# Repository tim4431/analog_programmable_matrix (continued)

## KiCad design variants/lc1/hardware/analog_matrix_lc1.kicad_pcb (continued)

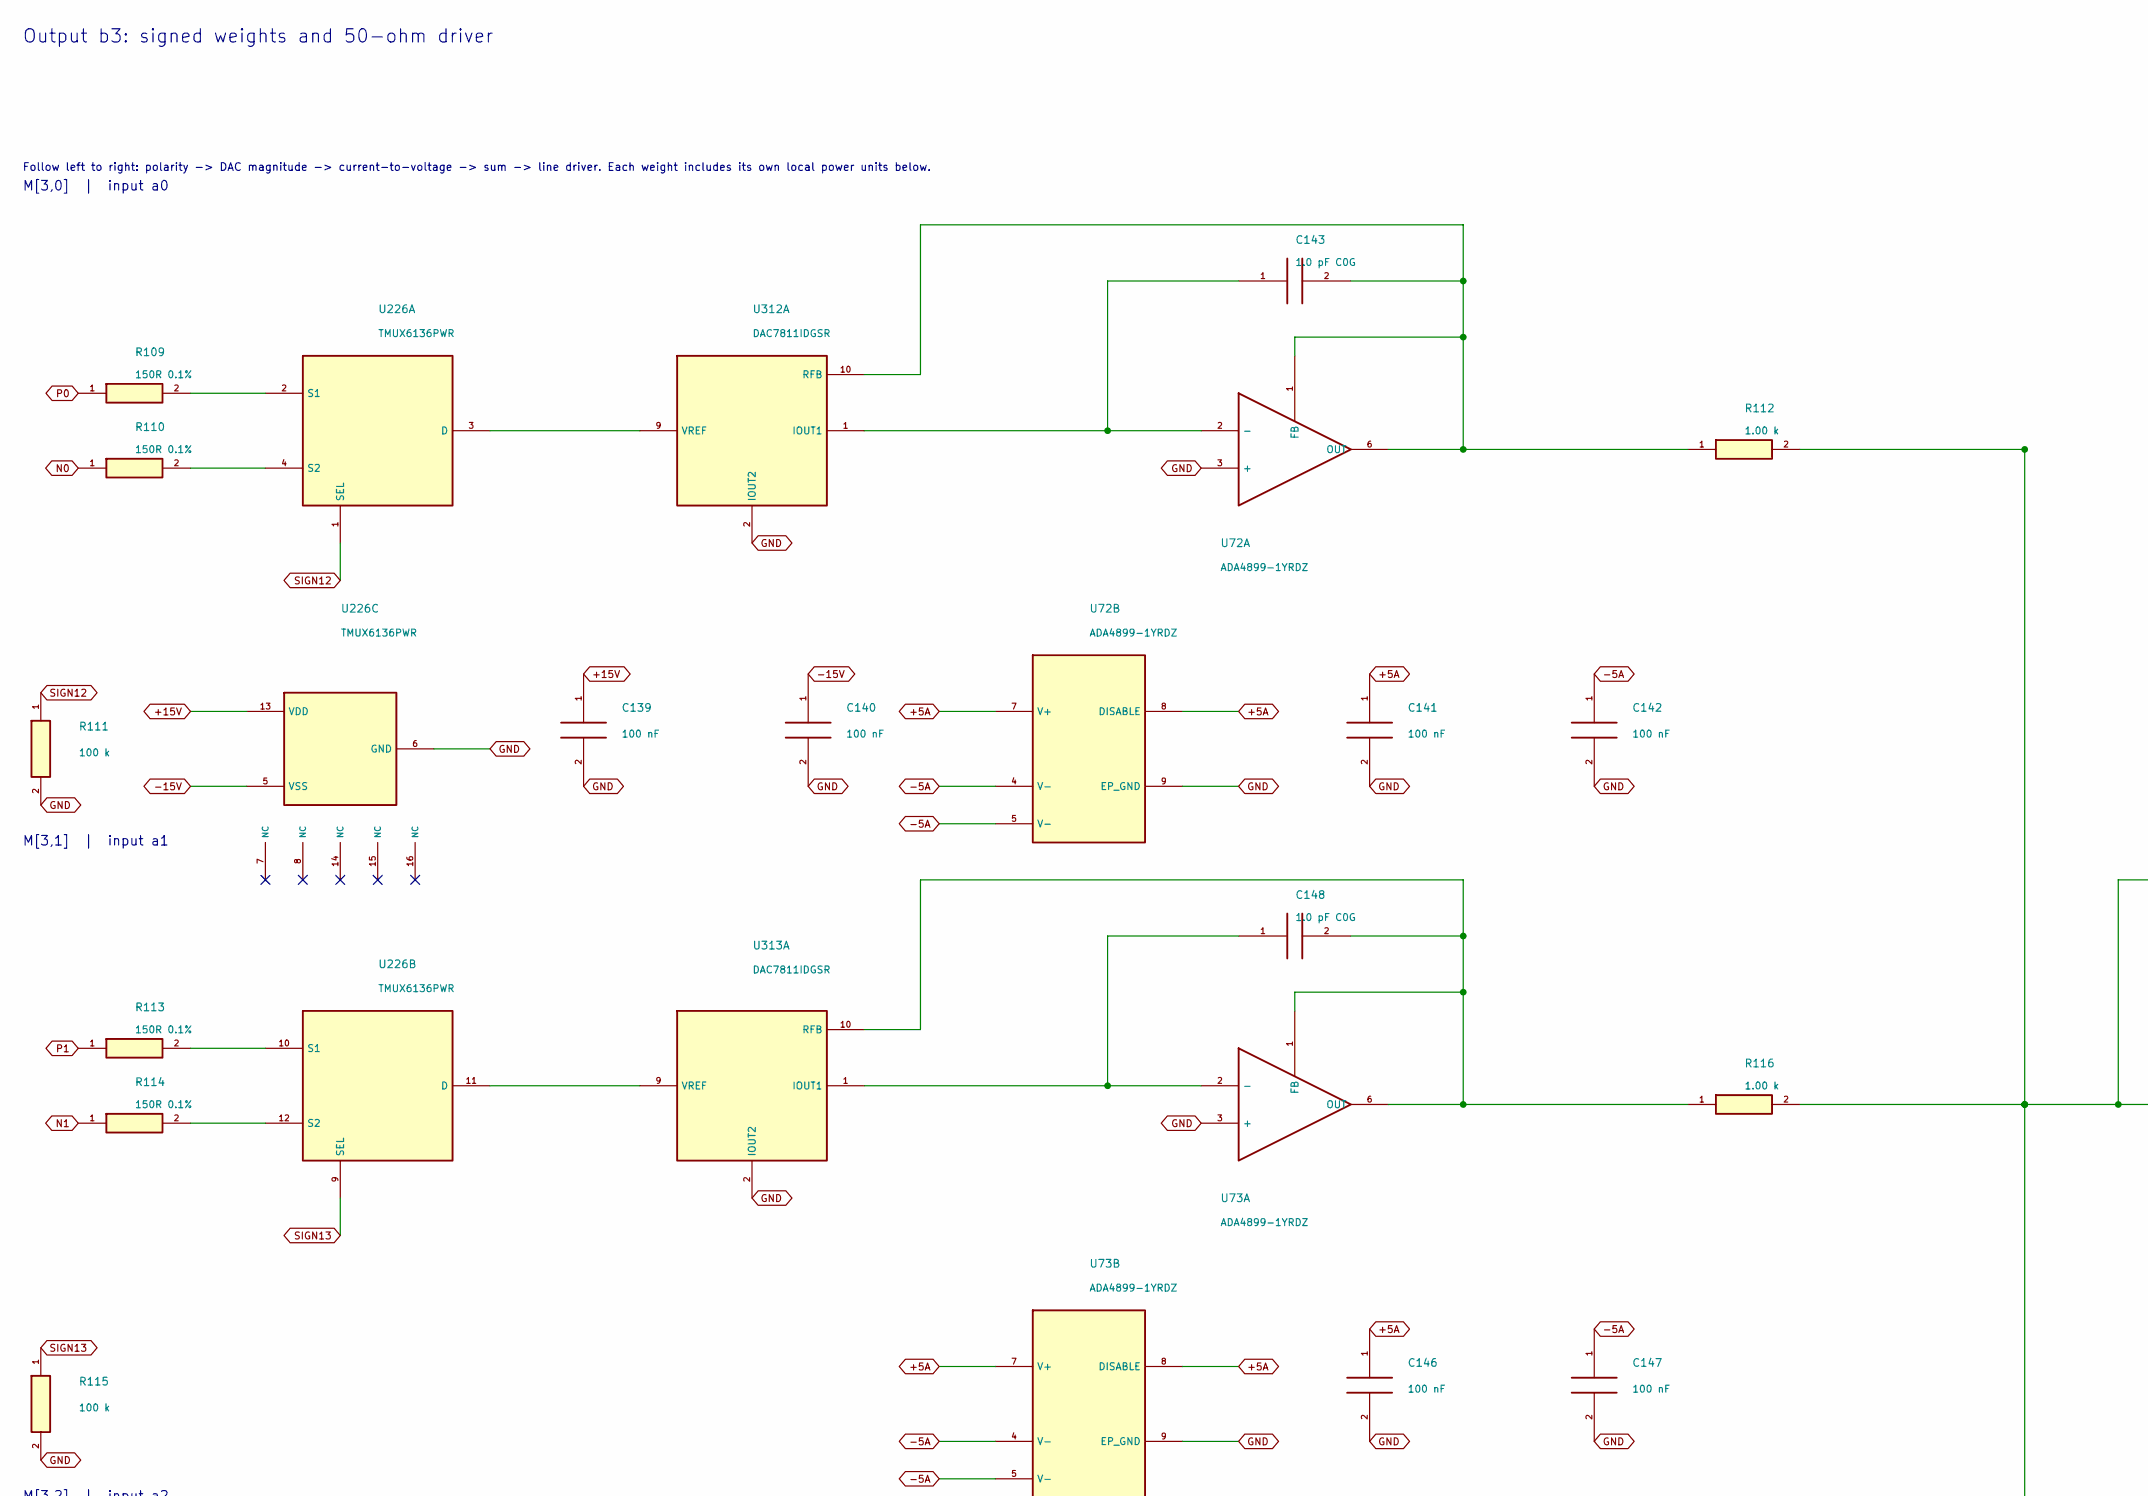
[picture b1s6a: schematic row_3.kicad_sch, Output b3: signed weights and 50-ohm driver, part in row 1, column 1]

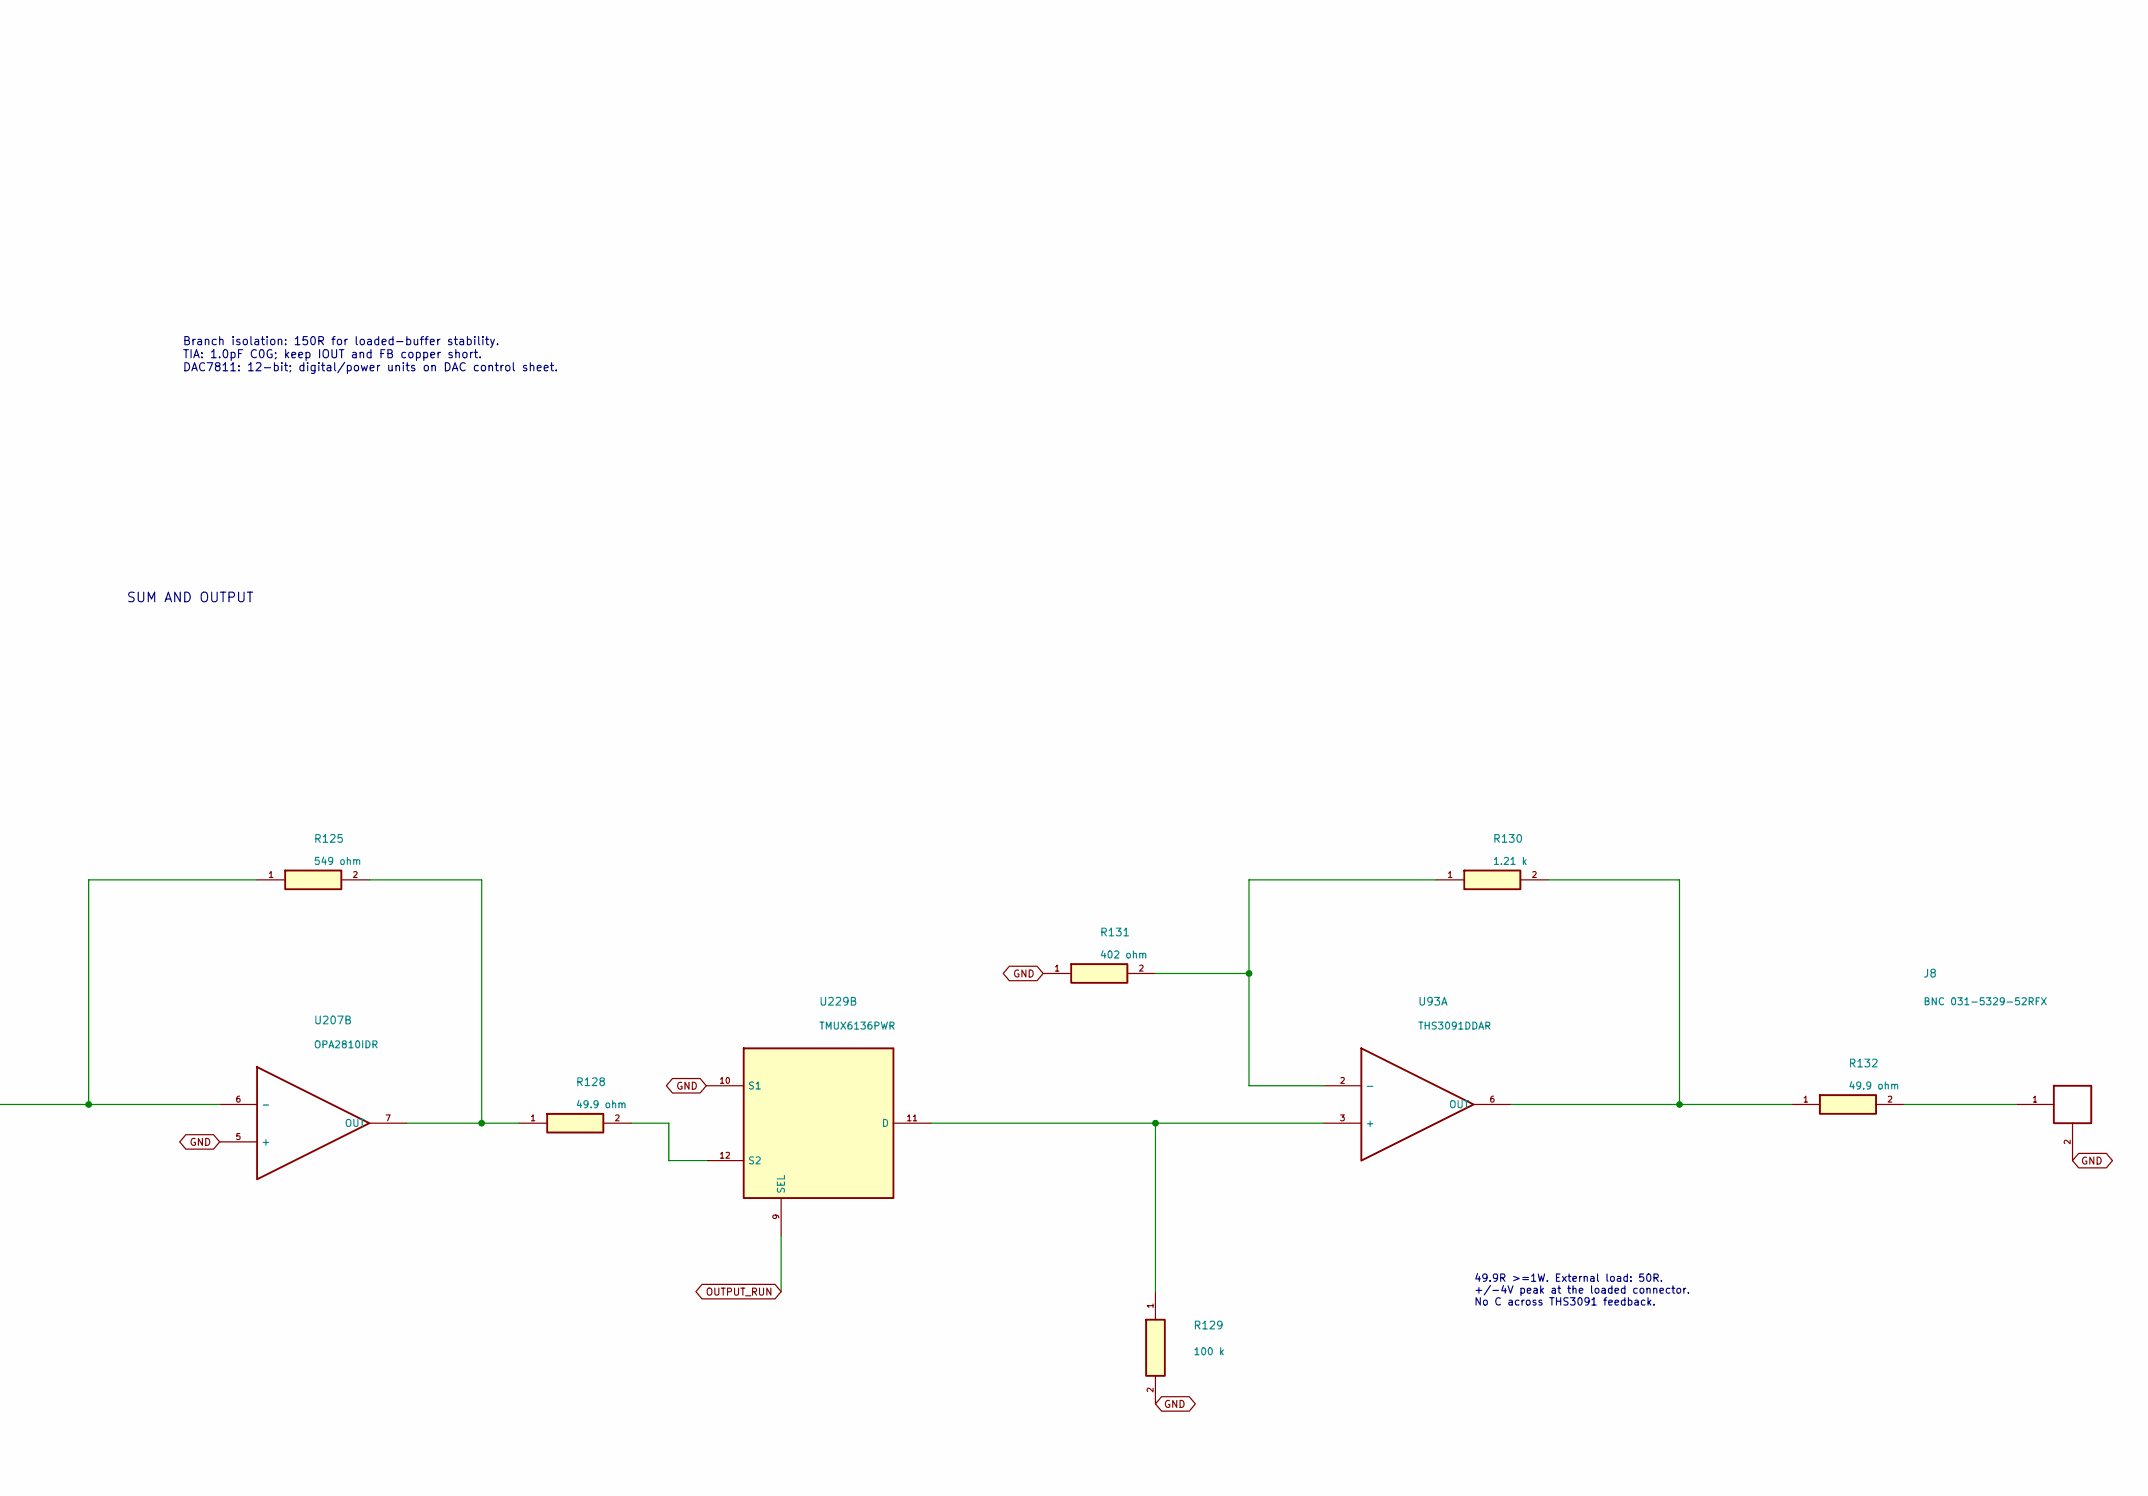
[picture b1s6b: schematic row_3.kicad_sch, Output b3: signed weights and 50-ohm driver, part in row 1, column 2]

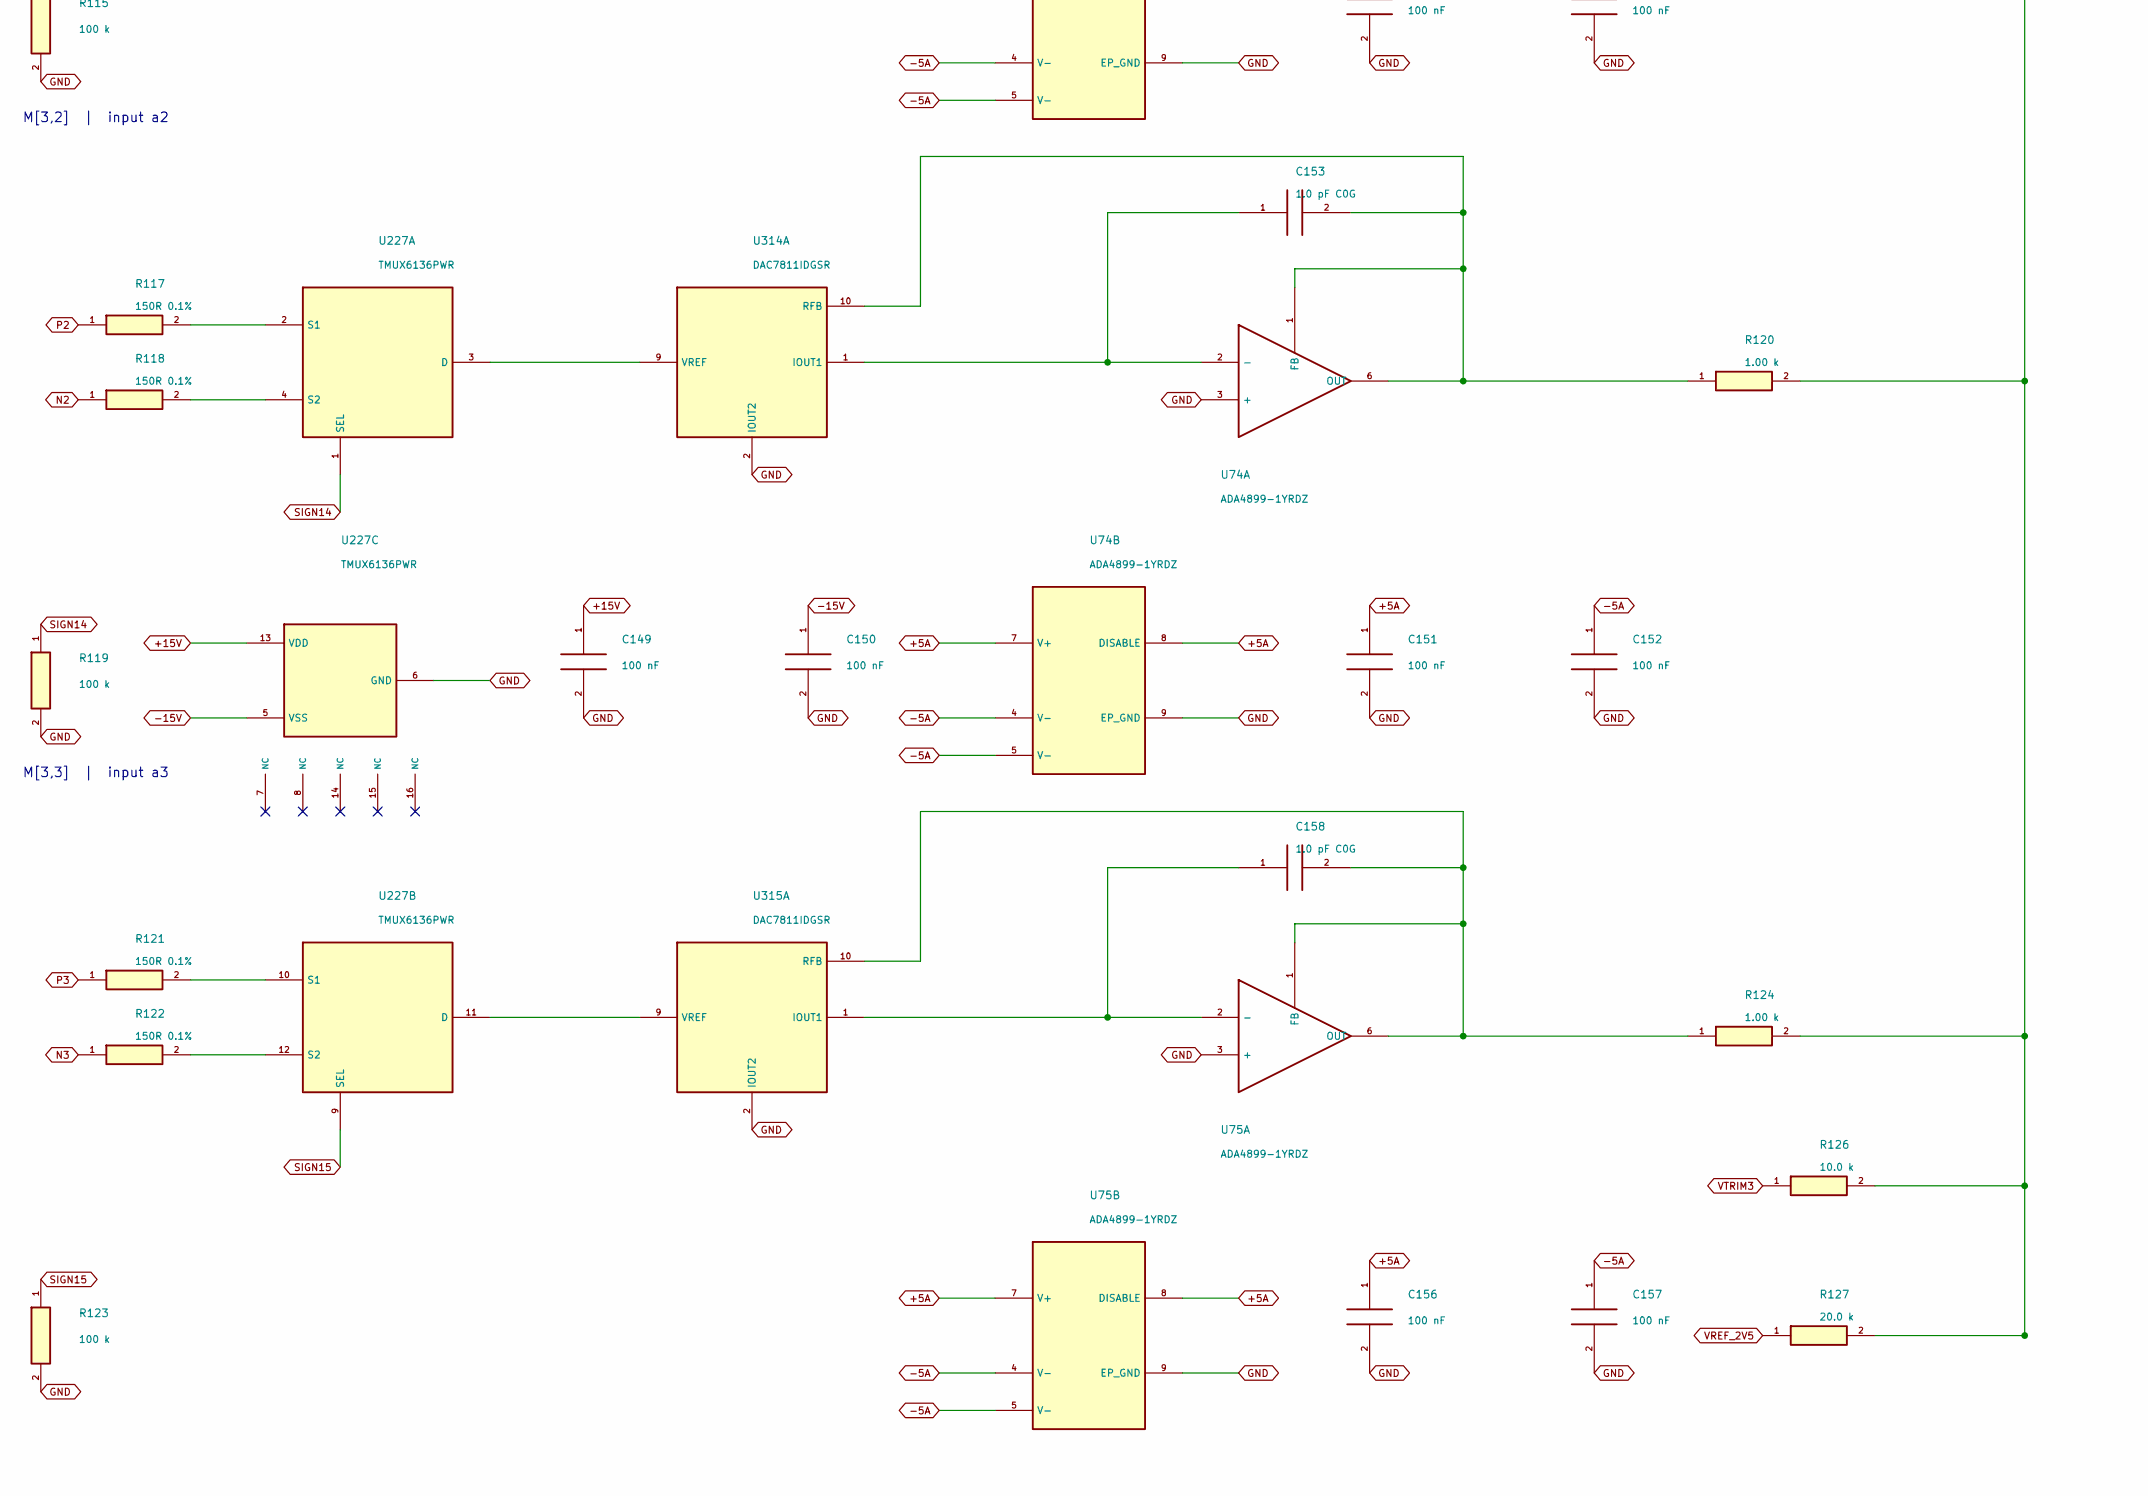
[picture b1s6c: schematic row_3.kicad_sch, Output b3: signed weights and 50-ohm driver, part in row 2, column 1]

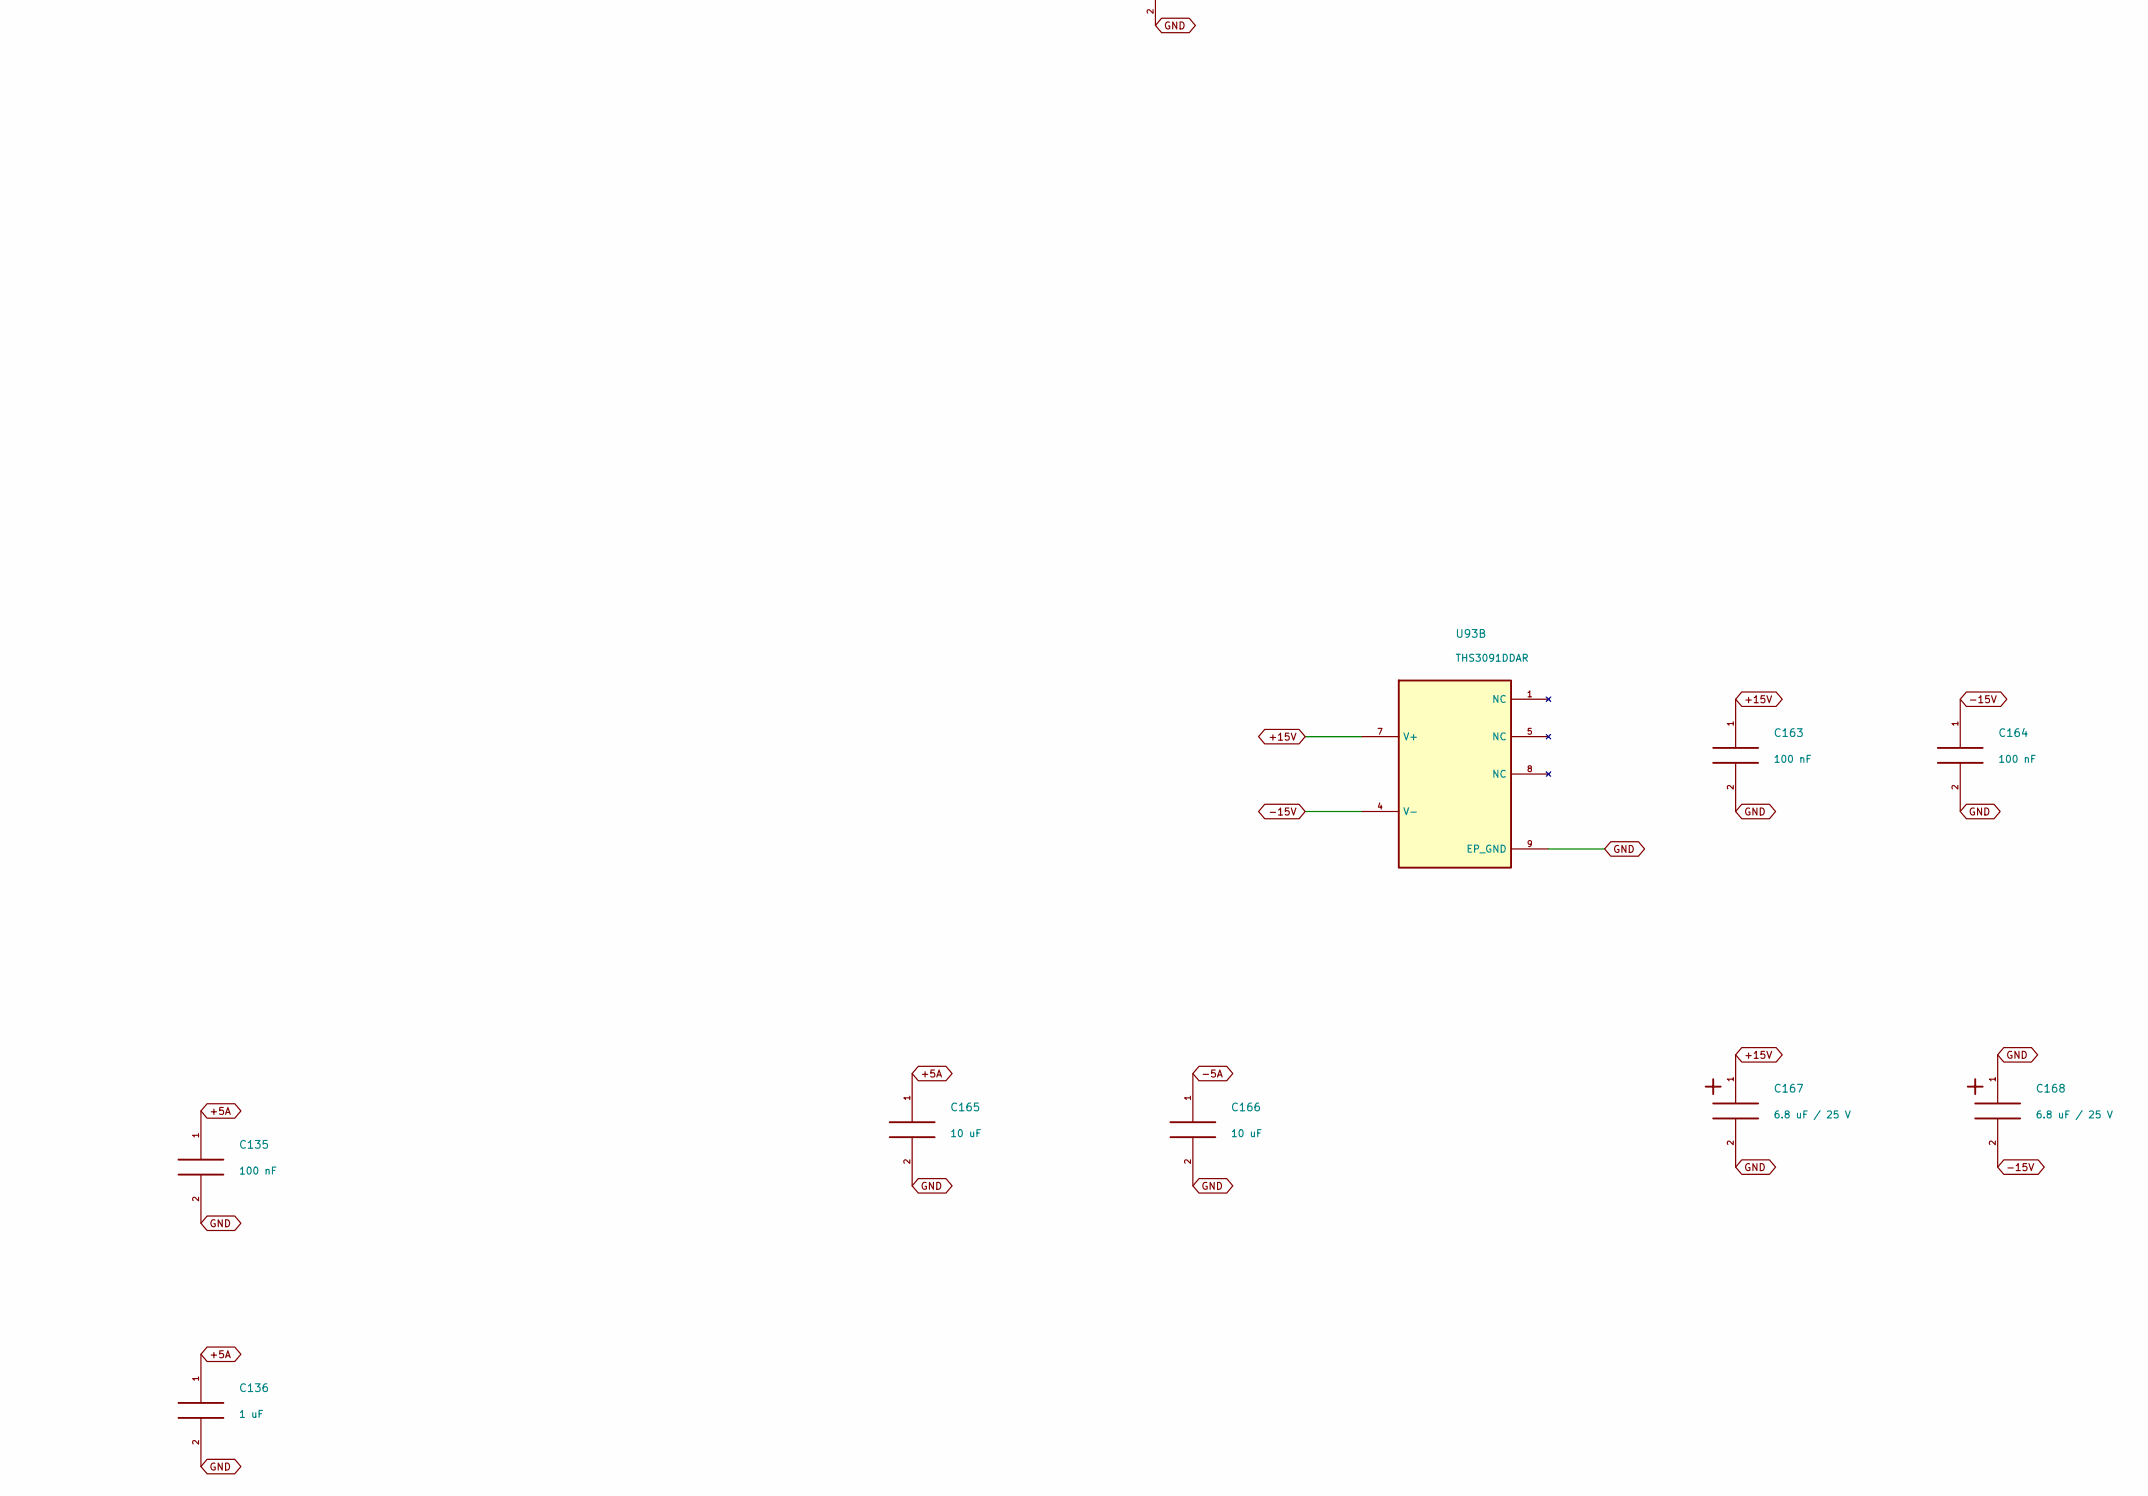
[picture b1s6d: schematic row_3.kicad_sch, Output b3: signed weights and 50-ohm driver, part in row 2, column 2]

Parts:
C135, C139, C140, C141, C142, C146, C147, C149, C150, C151, C152, C156, C157, C163, C164: 100 nF; C_0603_1608Metric; Rating 25V X7R minimum; effective C after bias
C136: 1 uF; C_0805_2012Metric; Rating 25V X7R minimum; effective C after bias
C143, C148, C153, C158: 1.0 pF C0G; C_0402_1005Metric; Rating 50V C0G, +/-0.1pF; stray capacitance in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
C165, C166: 10 uF; C_0805_2012Metric; Rating 25V X7R minimum; effective C after bias
C167, C168: 6.8 uF / 25 V; CP_EIA-3216-18_Kemet-A; Rating 25V polarized
J8: BNC 031-5329-52RFX; BNC_Amphenol_031-5329-52RFX_Vertical
R109, R110, R113, R114, R117, R118, R121, R122: 150R 0.1%; R_0603_1608Metric; Rating 0.1%, <=25ppm/C; 0.1W minimum
R111, R115, R119, R123, R129: 100 k; R_0603_1608Metric; Rating 0.1%, <=25ppm/C; 0.1W minimum
R112, R116, R120, R124: 1.00 k; R_0603_1608Metric; Rating 0.1%, <=25ppm/C; 0.1W minimum
R125: 549 ohm; R_0603_1608Metric; Rating 0.1%, <=25ppm/C; 0.1W minimum
R126: 10.0 k; R_0603_1608Metric; Rating 0.1%, <=25ppm/C; 0.1W minimum
R127: 20.0 k; R_0603_1608Metric; Rating 0.1%, <=25ppm/C; 0.1W minimum
R128: 49.9 ohm; R_0603_1608Metric; Rating 0.1%, <=25ppm/C; 0.1W minimum
R130: 1.21 k; R_0603_1608Metric; Rating 0.1%, <=25ppm/C; 0.1W minimum
R131: 402 ohm; R_0603_1608Metric; Rating 0.1%, <=25ppm/C; 0.1W minimum
R132: 49.9 ohm; R_2512_6332Metric; Rating 0.1%, <=25ppm/C; >=1W
U72, U73, U74, U75: ADA4899-1YRDZ; ADA4899_RD8_EP2.29x2.29
U93: THS3091DDAR; SOIC-8-1EP_3.9x4.9mm_P1.27mm_EP2.95x4.9mm_Mask2.71x3.4mm_Th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
U207: OPA2810IDR; SOIC-8_3.9x4.9mm_P1.27mm
U226, U227, U229: TMUX6136PWR; TSSOP-16_4.4x5mm_P0.65mm
U312, U313, U314, U315: DAC7811IDGSR; VSSOP-10_3x3mm_P0.5mm

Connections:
+5A: C135.1, C136.1, C141.1, C146.1, C151.1, C156.1, C165.1, U72.7 (V+), U72.8 (DISABLE), U73.7 (V+), U73.8 (DISABLE), U74.7 (V+), U74.8 (DISABLE), U75.7 (V+), U75.8 (DISABLE); also elsewhere on the board
+15V: C139.1, C149.1, C163.1, C167.1, U93.7 (V+), U226.13 (VDD), U227.13 (VDD); also elsewhere on the board
-5A: C142.1, C147.1, C152.1, C157.1, C166.1, U72.4 (V-), U72.5 (V-), U73.4 (V-), U73.5 (V-), U74.4 (V-), U74.5 (V-), U75.4 (V-), U75.5 (V-); also elsewhere on the board
-15V: C140.1, C150.1, C164.1, C168.2, U93.4 (V-), U226.5 (VSS), U227.5 (VSS); also elsewhere on the board
GND: C135.2, C136.2, C139.2, C140.2, C141.2, C142.2, C146.2, C147.2, C149.2, C150.2, C151.2, C152.2, C156.2, C157.2, C163.2, C164.2, C165.2, C166.2, C167.2, C168.1, J8.2, R111.2, R115.2, R119.2, R123.2, R129.2, R131.1, U72.3 (+), U72.9 (EP_GND), U73.3 (+), U73.9 (EP_GND), U74.3 (+), U74.9 (EP_GND), U75.3 (+), U75.9 (EP_GND), U93.9 (EP_GND), U207.5 (+), U226.6 (GND), U227.6 (GND), U229.10 (S1), U312.2 (IOUT2), U313.2 (IOUT2), U314.2 (IOUT2), U315.2 (IOUT2); also elsewhere on the board
N0: R110.1; also elsewhere on the board
N1: R114.1; also elsewhere on the board
N2: R118.1; also elsewhere on the board
N3: R122.1; also elsewhere on the board
unnamed: J8.1, R132.2
unnamed: R130.1, R131.2, U93.2 (-)
unnamed: R130.2, R132.1, U93.6 (OUT)
unnamed: R112.2, R116.2, R120.2, R124.2, R125.1, R126.2, R127.2, U207.6 (-)
unnamed: R125.2, R128.1, U207.7 (OUT)
unnamed: U226.3 (D), U312.9 (VREF)
unnamed: R109.2, U226.2 (S1)
unnamed: R110.2, U226.4 (S2)
unnamed: U226.11 (D), U313.9 (VREF)
unnamed: R113.2, U226.10 (S1)
unnamed: R114.2, U226.12 (S2)
unnamed: U227.3 (D), U314.9 (VREF)
unnamed: R117.2, U227.2 (S1)
unnamed: R118.2, U227.4 (S2)
unnamed: U227.11 (D), U315.9 (VREF)
unnamed: R121.2, U227.10 (S1)
unnamed: R122.2, U227.12 (S2)
unnamed: R129.1, U93.3 (+), U229.11 (D)
unnamed: R128.2, U229.12 (S2)
unnamed: C143.1, U72.2 (-), U312.1 (IOUT1)
unnamed: C143.2, R112.1, U72.1 (FB), U72.6 (OUT), U312.10 (RFB)
unnamed: C148.1, U73.2 (-), U313.1 (IOUT1)
unnamed: C148.2, R116.1, U73.1 (FB), U73.6 (OUT), U313.10 (RFB)
unnamed: C153.1, U74.2 (-), U314.1 (IOUT1)
unnamed: C153.2, R120.1, U74.1 (FB), U74.6 (OUT), U314.10 (RFB)
unnamed: C158.1, U75.2 (-), U315.1 (IOUT1)
unnamed: C158.2, R124.1, U75.1 (FB), U75.6 (OUT), U315.10 (RFB)
OUTPUT_RUN: U229.9 (SEL); also elsewhere on the board
P0: R109.1; also elsewhere on the board
P1: R113.1; also elsewhere on the board
P2: R117.1; also elsewhere on the board
P3: R121.1; also elsewhere on the board
SIGN12: R111.1, U226.1 (SEL); also elsewhere on the board
SIGN13: R115.1, U226.9 (SEL); also elsewhere on the board
SIGN14: R119.1, U227.1 (SEL); also elsewhere on the board
SIGN15: R123.1, U227.9 (SEL); also elsewhere on the board
VREF_2V5: R127.1; also elsewhere on the board
VTRIM3: R126.1; also elsewhere on the board

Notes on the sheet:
Output b3: signed weights and 50-ohm driver
Follow left to right: polarity -> DAC magnitude -> current-to-voltage -> sum -> line driver. Each weight includes its own local power units below.
M[3,0] | input a0
M[3,1] | input a1
M[3,2] | input a2
M[3,3] | input a3
SUM AND OUTPUT
49.9R >=1W. External load: 50R. +/-4V peak at the loaded connector. No C across THS3091 feedback.
Branch isolation: 150R for loaded-buffer stability. TIA: 1.0pF C0G; keep IOUT and FB copper short. DAC7811: 12-bit; digital/power units on DAC control sheet.

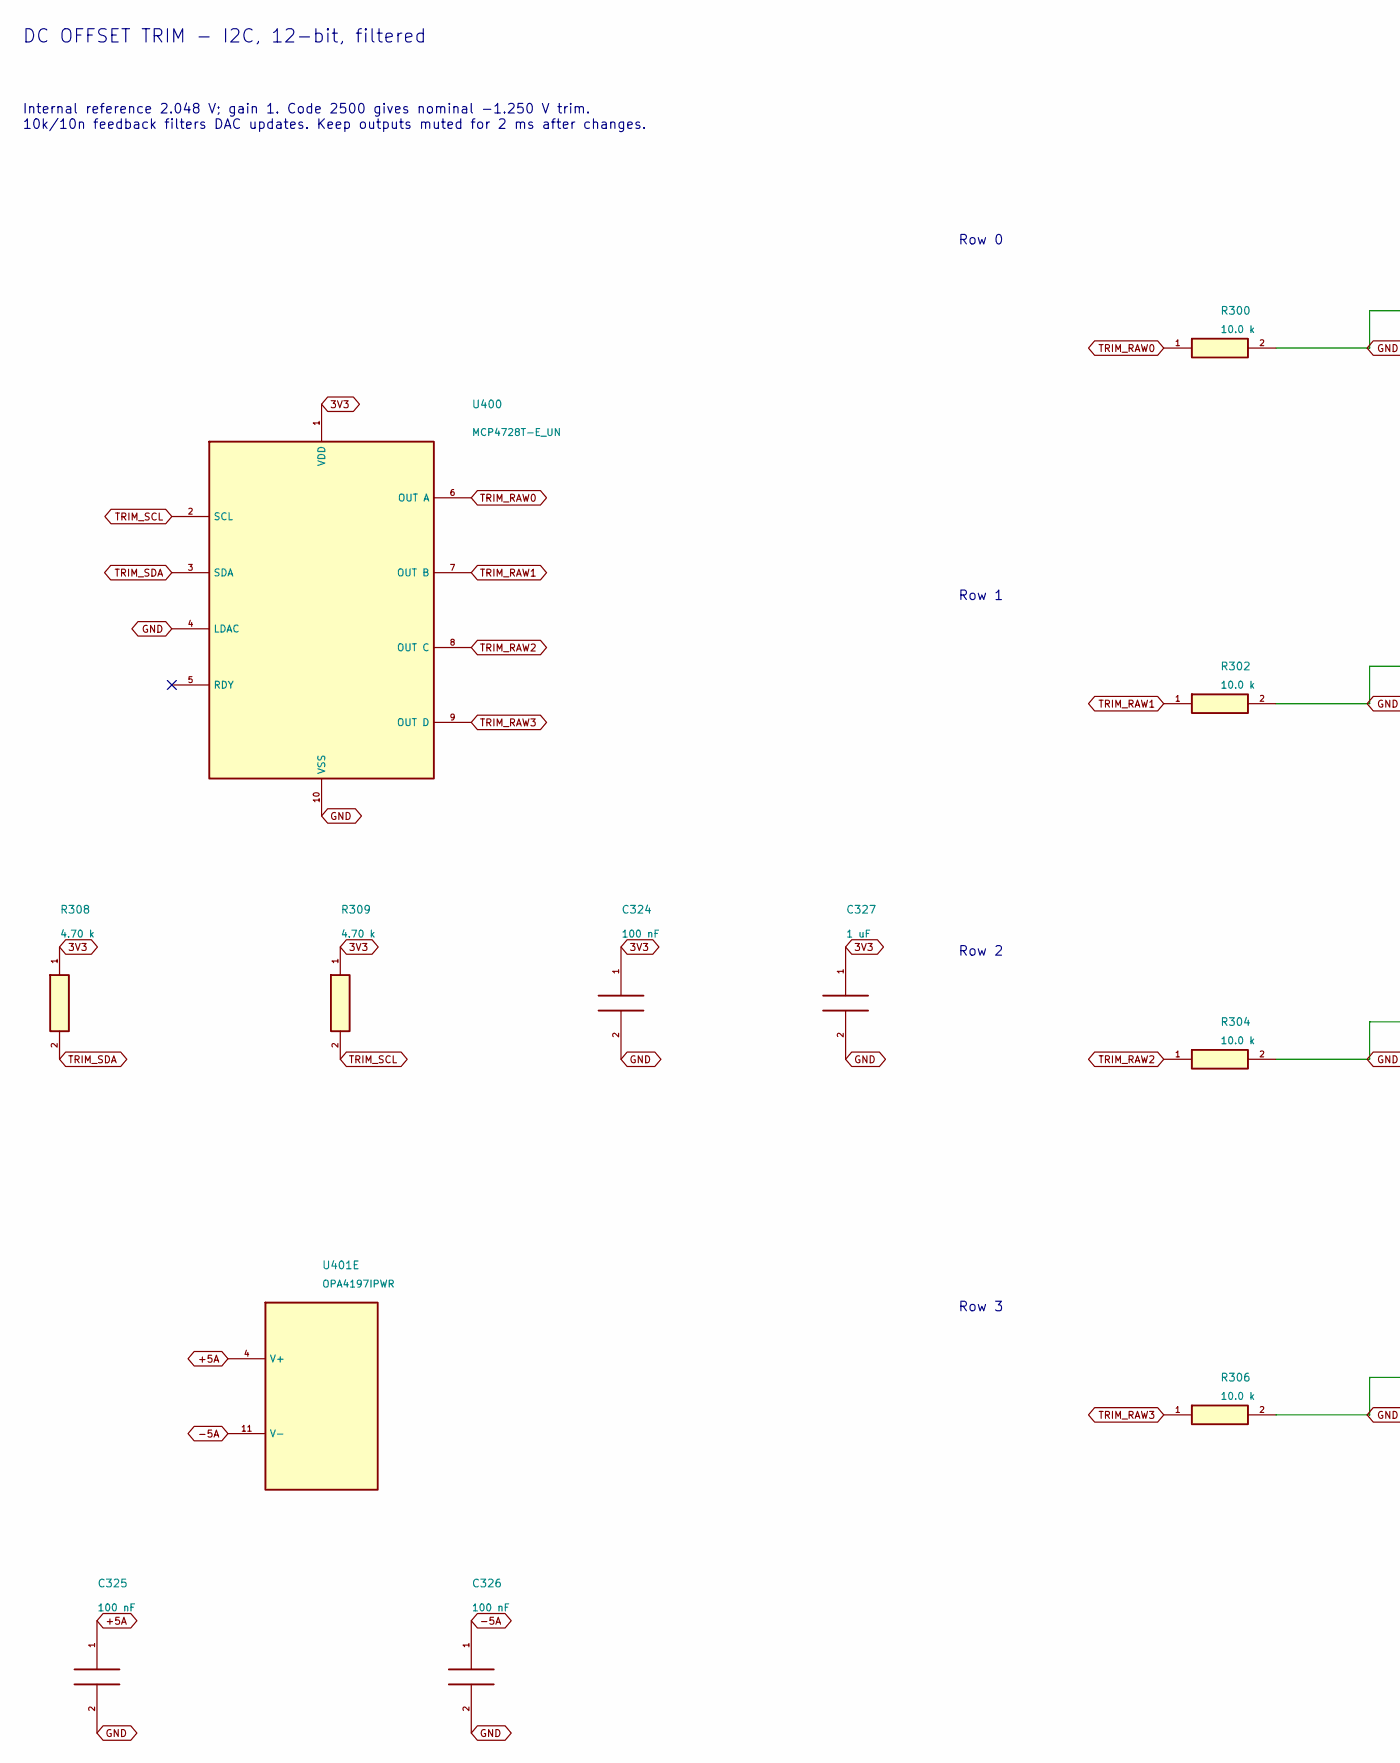
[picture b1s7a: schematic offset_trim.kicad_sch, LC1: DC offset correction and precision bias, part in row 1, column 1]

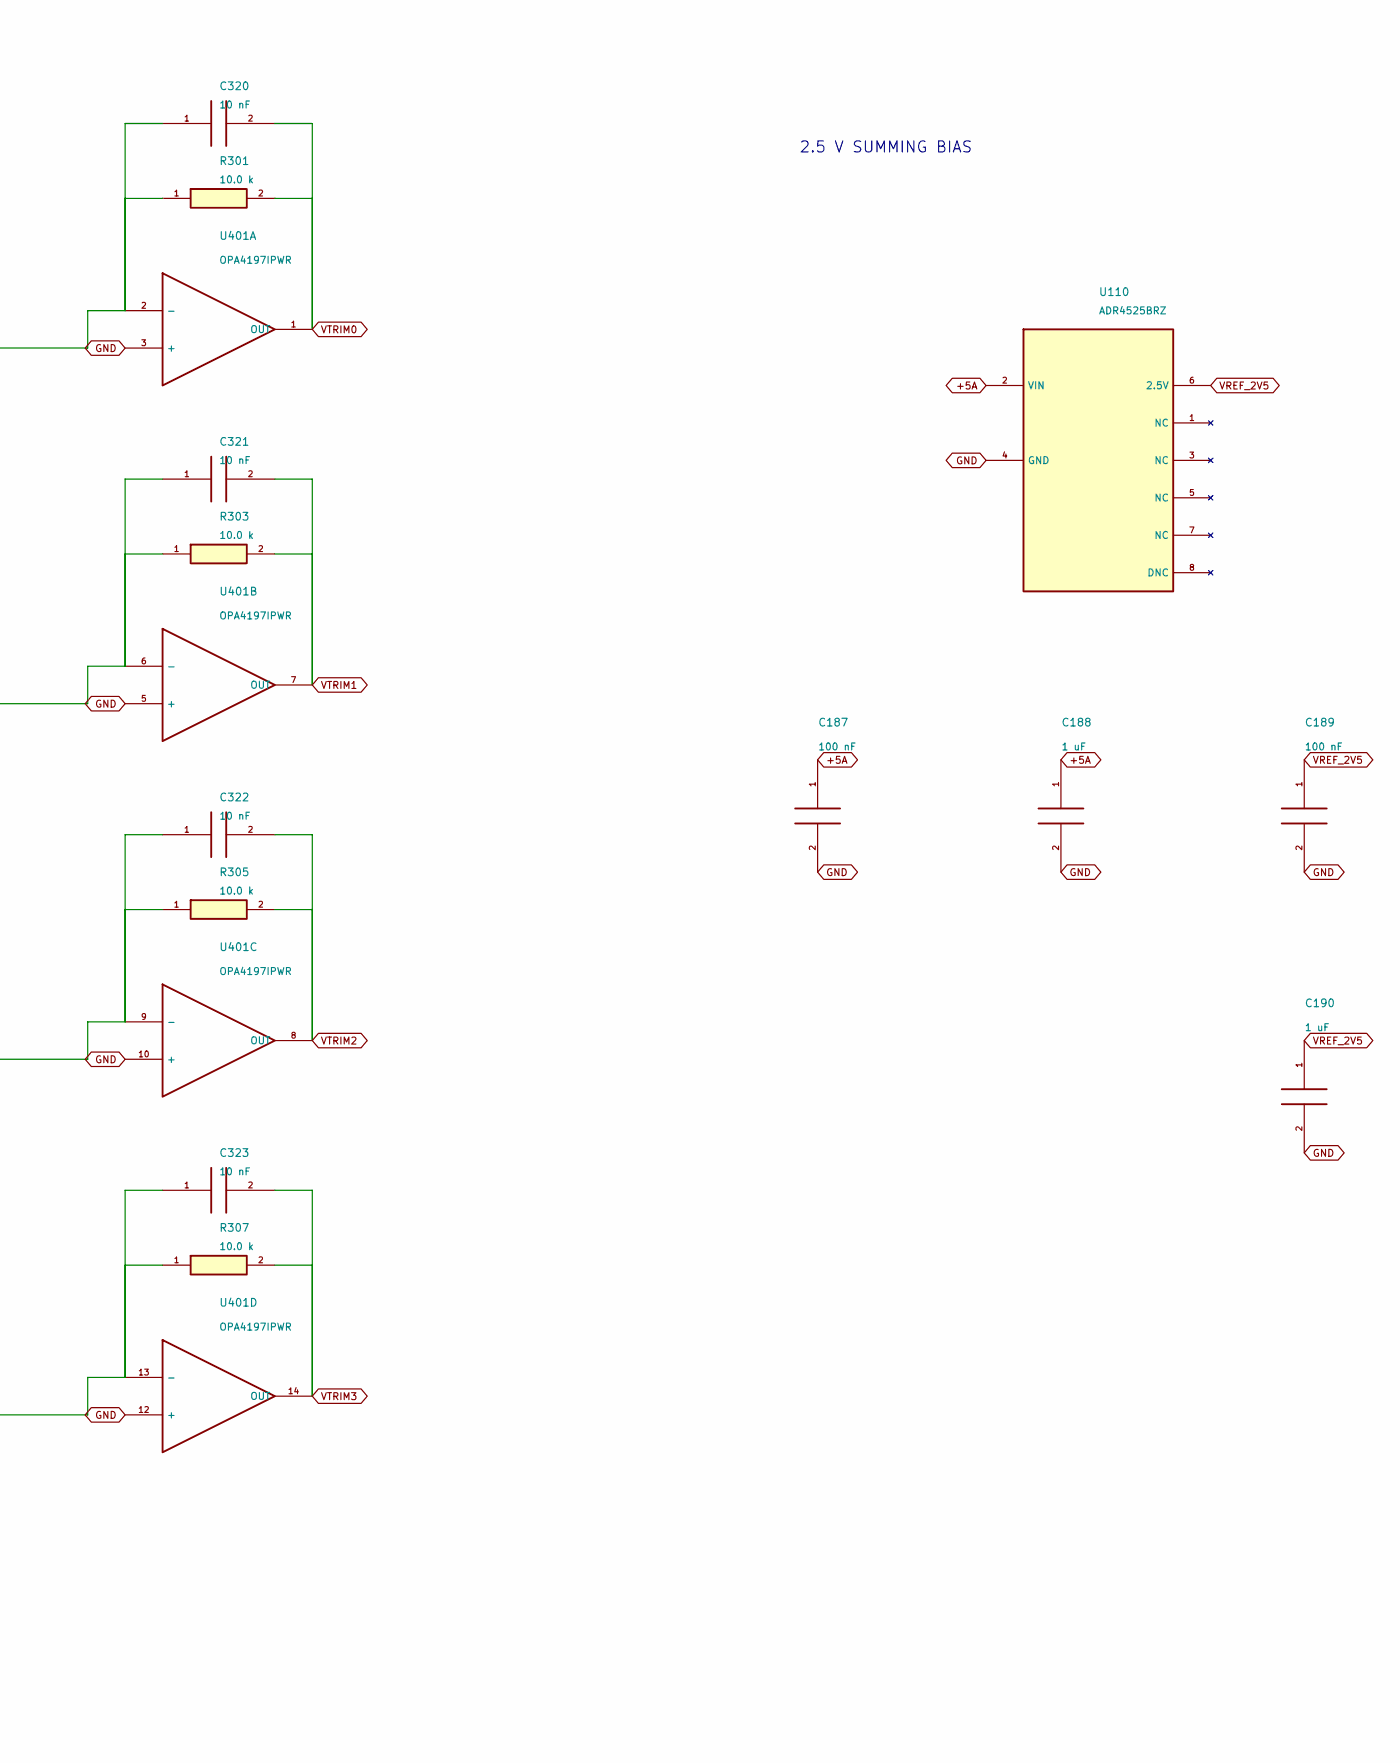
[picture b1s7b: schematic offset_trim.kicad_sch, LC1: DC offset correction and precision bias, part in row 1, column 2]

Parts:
C187, C189: 100 nF; C_0603_1608Metric; Rating 25V X7R minimum; effective C after bias
C188, C190: 1 uF; C_0805_2012Metric; Rating 25V X7R minimum; effective C after bias
C320, C321, C322, C323: 10 nF; C_0603_1608Metric; Rating 25V X7R; trim filter only
C324, C325, C326: 100 nF; C_0603_1608Metric; Rating 25V X7R
C327: 1 uF; C_0603_1608Metric; Rating 25V X7R
R300, R301, R302, R303, R304, R305, R306, R307: 10.0 k; R_0603_1608Metric; Rating 0.1%, 25ppm/C
R308, R309: 4.70 k; R_0603_1608Metric; Rating 1%, 0.1W
U110: ADR4525BRZ; SOIC-8_3.9x4.9mm_P1.27mm
U400: MCP4728T-E_UN; MSOP-10_3x3mm_P0.5mm
U401: OPA4197IPWR; TSSOP-14_4.4x5mm_P0.65mm

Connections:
3V3: C324.1, C327.1, R308.1, R309.1, U400.1 (VDD); also elsewhere on the board
+5A: C187.1, C188.1, C325.1, U110.2 (VIN), U401.4 (V+); also elsewhere on the board
-5A: C326.1, U401.11 (V-); also elsewhere on the board
GND: C187.2, C188.2, C189.2, C190.2, C324.2, C325.2, C326.2, C327.2, U110.4 (GND), U400.4 (LDAC), U400.10 (VSS), U401.3 (+), U401.5 (+), U401.10 (+), U401.12 (+); also elsewhere on the board
unnamed: C320.1, R300.2, R301.1, U401.2 (-)
unnamed: C321.1, R302.2, R303.1, U401.6 (-)
unnamed: C322.1, R304.2, R305.1, U401.9 (-)
unnamed: C323.1, R306.2, R307.1, U401.13 (-)
TRIM_RAW0: R300.1, U400.6 (OUT A)
TRIM_RAW1: R302.1, U400.7 (OUT B)
TRIM_RAW2: R304.1, U400.8 (OUT C)
TRIM_RAW3: R306.1, U400.9 (OUT D)
TRIM_SCL: R309.2, U400.2 (SCL); also elsewhere on the board
TRIM_SDA: R308.2, U400.3 (SDA); also elsewhere on the board
VREF_2V5: C189.1, C190.1, U110.6 (2.5V); also elsewhere on the board
VTRIM0: C320.2, R301.2, U401.1 (OUT); also elsewhere on the board
VTRIM1: C321.2, R303.2, U401.7 (OUT); also elsewhere on the board
VTRIM2: C322.2, R305.2, U401.8 (OUT); also elsewhere on the board
VTRIM3: C323.2, R307.2, U401.14 (OUT); also elsewhere on the board

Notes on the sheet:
DC OFFSET TRIM - I2C, 12-bit, filtered
Internal reference 2.048 V; gain 1. Code 2500 gives nominal -1.250 V trim. 10k/10n feedback filters DAC updates. Keep outputs muted for 2 ms after changes.
Row 0
Row 1
Row 2
Row 3
2.5 V SUMMING BIAS
